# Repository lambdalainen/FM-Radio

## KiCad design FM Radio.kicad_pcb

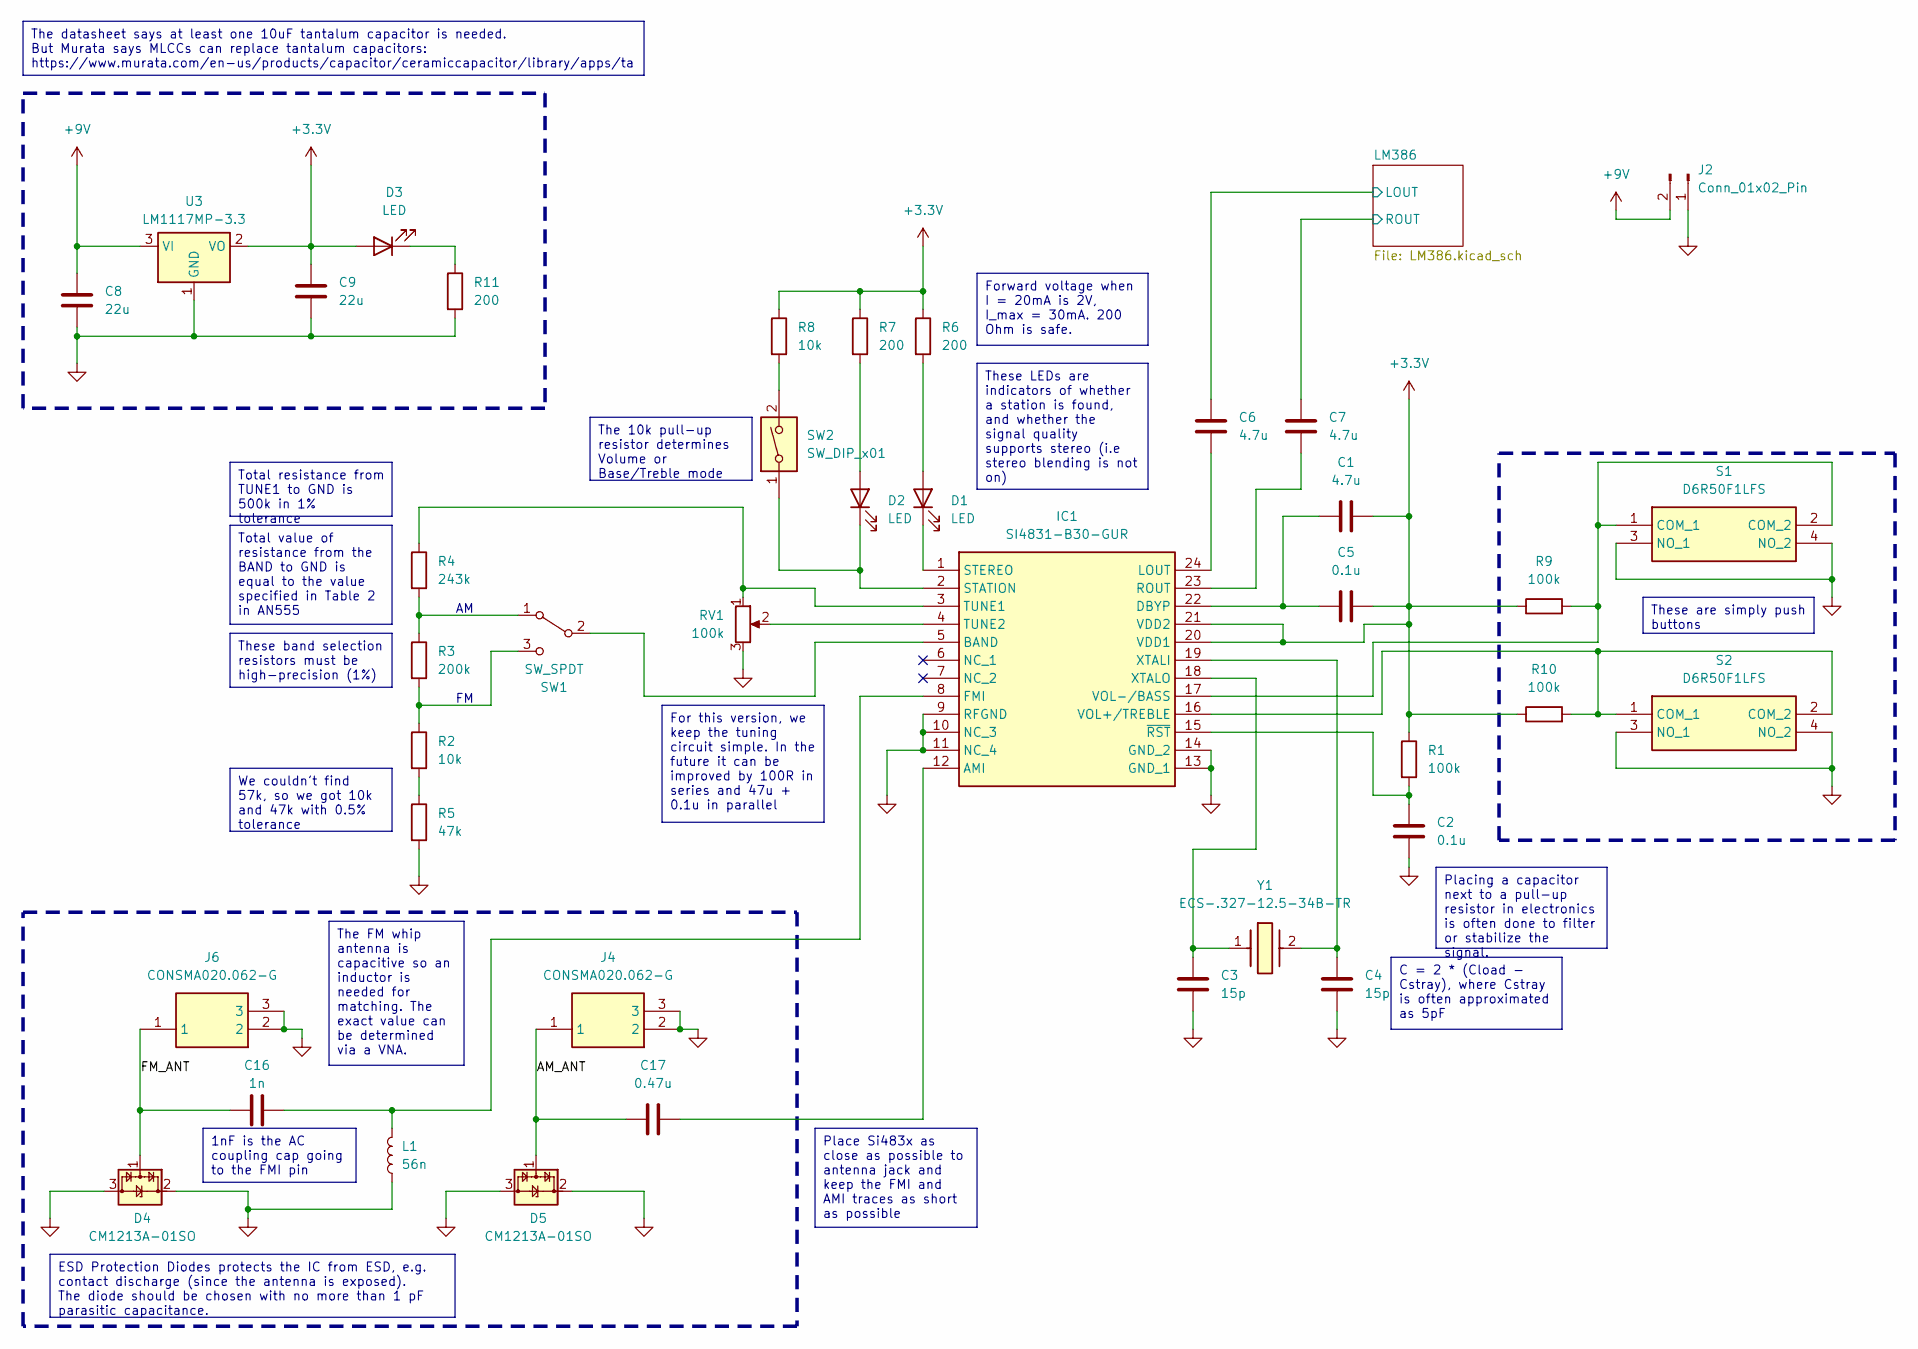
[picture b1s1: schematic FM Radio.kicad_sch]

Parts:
C1, C6, C7: 4.7u; C_0603_1608Metric
C2, C5: 0.1u; C_0603_1608Metric
C3, C4: 15p; C_0603_1608Metric
C8: 22u; C_0805_2012Metric
C9: 22u; CAPC2012X145N
C16: 1n; C_0603_1608Metric
C17: 0.47u; C_0603_1608Metric
D1, D2, D3: LED; LED_0603_1608Metric
D4, D5: CM1213A-01SO; SOT-23-3
IC1: SI4831-B30-GUR; SOP64P600X175-24N; Manufacturer_Part_Number SI4831-B30-GUR; Mouser Part Number 634-SI4831-B30-GUR
J2: Conn_01x02_Pin; PinHeader_1x02_P2.54mm_Vertical
J4, J6: CONSMA020.062-G; CONSMA020062G; Manufacturer_Part_Number CONSMA020.062-G; Mouser Part Number 712-CONSMA020.062-G
L1: 56n; L_0603_1608Metric
R1, R9, R10: 100k; R_0603_1608Metric
R2: 10k; R_0603_1608Metric
R3: 200k; R_0603_1608Metric
R4: 243k; R_0603_1608Metric
R5: 47k; R_0603_1608Metric
R6: 200; RESC1608X55N
R7, R11: 200; R_0603_1608Metric
R8: 10k; R_0603_1608Metric_Pad0.98x0.95mm_HandSolder
RV1: 100k; 91A1AB28B13L
S1, S2: D6R50F1LFS; D6R40F1LFS; Manufacturer_Part_Number D6R50F1LFS; Mouser Part Number 611-D6R50F1LFS
SW1: SW_SPDT; SW_SPDT_PCM12
SW2: SW_DIP_x01; DS01254L01BE
U3: LM1117MP-3.3; SOT-223-3_TabPin2
Y1: ECS-.327-12.5-34B-TR; ECX-31B; Manufacturer_Part_Number ECS-.327-12.5-34B-TR; Mouser Part Number 520-327-12.5-34B

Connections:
+3.3V: C1.2, C5.2, C9.2, D3.2 (A), IC1.20 (VDD1), IC1.21 (VDD2), R1.1, R6.1, R7.1, R8.1, R9.1, R10.1, U3.2 (VO)
/AM_ANT: C17.2, D5.1 (CH1), J4.1
/FM_ANT: C16.2, D4.1 (CH1), J6.1
/LM386/LOUT: C6.2; also elsewhere on the board
/LM386/ROUT: C7.2; also elsewhere on the board
GND: C2.2, C3.2, C4.2, C8.1, C9.1, D4.2 (VP), D4.3 (VN), D5.2 (VP), D5.3 (VN), IC1.9 (RFGND), IC1.10 (NC_3), IC1.11 (NC_4), IC1.13 (GND_1), IC1.14 (GND_2), J2.1, J4.2, J4.3, J6.2, J6.3, L1.1, R5.2, R11.2, RV1.3, S1.3 (NO_1), S1.4 (NO_2), S2.3 (NO_1), S2.4 (NO_2), U3.1 (GND); also elsewhere on the board
unnamed: D1.2 (A), R6.2
unnamed: D1.1 (K), IC1.1 (STEREO)
unnamed: D2.2 (A), R7.2
unnamed: D2.1 (K), IC1.2 (STATION), SW2.1
unnamed: D3.1 (K), R11.1
unnamed: C17.1, IC1.12 (AMI)
unnamed: IC1.5 (BAND), SW1.2 (B)
unnamed: C1.1, C5.1, IC1.22 (DBYP)
unnamed: C16.1, IC1.8 (FMI), L1.2
unnamed: C6.1, IC1.24 (LOUT)
unnamed: C7.1, IC1.23 (ROUT)
unnamed: IC1.3 (TUNE1), R4.1, RV1.1
unnamed: IC1.4 (TUNE2), RV1.2
unnamed: IC1.16 (VOL+/TREBLE), R10.2, S2.1 (COM_1), S2.2 (COM_2)
unnamed: IC1.17 (VOL-/BASS), R9.2, S1.1 (COM_1), S1.2 (COM_2)
unnamed: C4.1, IC1.19 (XTALI), Y1.2
unnamed: C3.1, IC1.18 (XTALO), Y1.1
unnamed: C2.1, IC1.15 (~RST), R1.2
unnamed: R2.2, R5.1
unnamed: R8.2, SW2.2
unnamed: R3.1, R4.2, SW1.1 (A)
unnamed: R2.1, R3.2, SW1.3 (C)

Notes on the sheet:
Placing a capacitor next to a pull-up resistor in electronics is often done to filter or stabilize the signal.
We couldn't find 57k, so we got 10k and 47k with 0.5% tolerance
These are simply push buttons
The FM whip antenna is capacitive so an inductor is needed for matching. The exact value can be determined via a VNA.
These LEDs are indicators of whether a station is found, and whether the signal quality supports stereo (i.e stereo blending is not on)
The 10k pull-up resistor determines Volume or Base/Treble mode
Place Si483x as close as possible to antenna jack and keep the FMI and AMI traces as short as possible
Total value of resistance from the BAND to GND is equal to the value specified in Table 2 in AN555
The datasheet says at least one 10uF tantalum capacitor is needed. But Murata says MLCCs can replace tantalum capacitors: https://www.murata.com/en-us/products/capacitor/ceramiccapacitor/library/apps/ta
These band selection resistors must be high-precision (1%)
For this version, we keep the tuning circuit simple. In the future it can be improved by 100R in series and 47u + 0.1u in parallel
1nF is the AC coupling cap going to the FMI pin
Forward voltage when I = 20mA is 2V, I_max = 30mA. 200 Ohm is safe.
Total resistance from TUNE1 to GND is 500k in 1% tolerance
ESD Protection Diodes protects the IC from ESD, e.g. contact discharge (since the antenna is exposed). The diode should be chosen with no more than 1 pF parasitic capacitance.
C = 2 * (Cload - Cstray), where Cstray is often approximated as 5pF

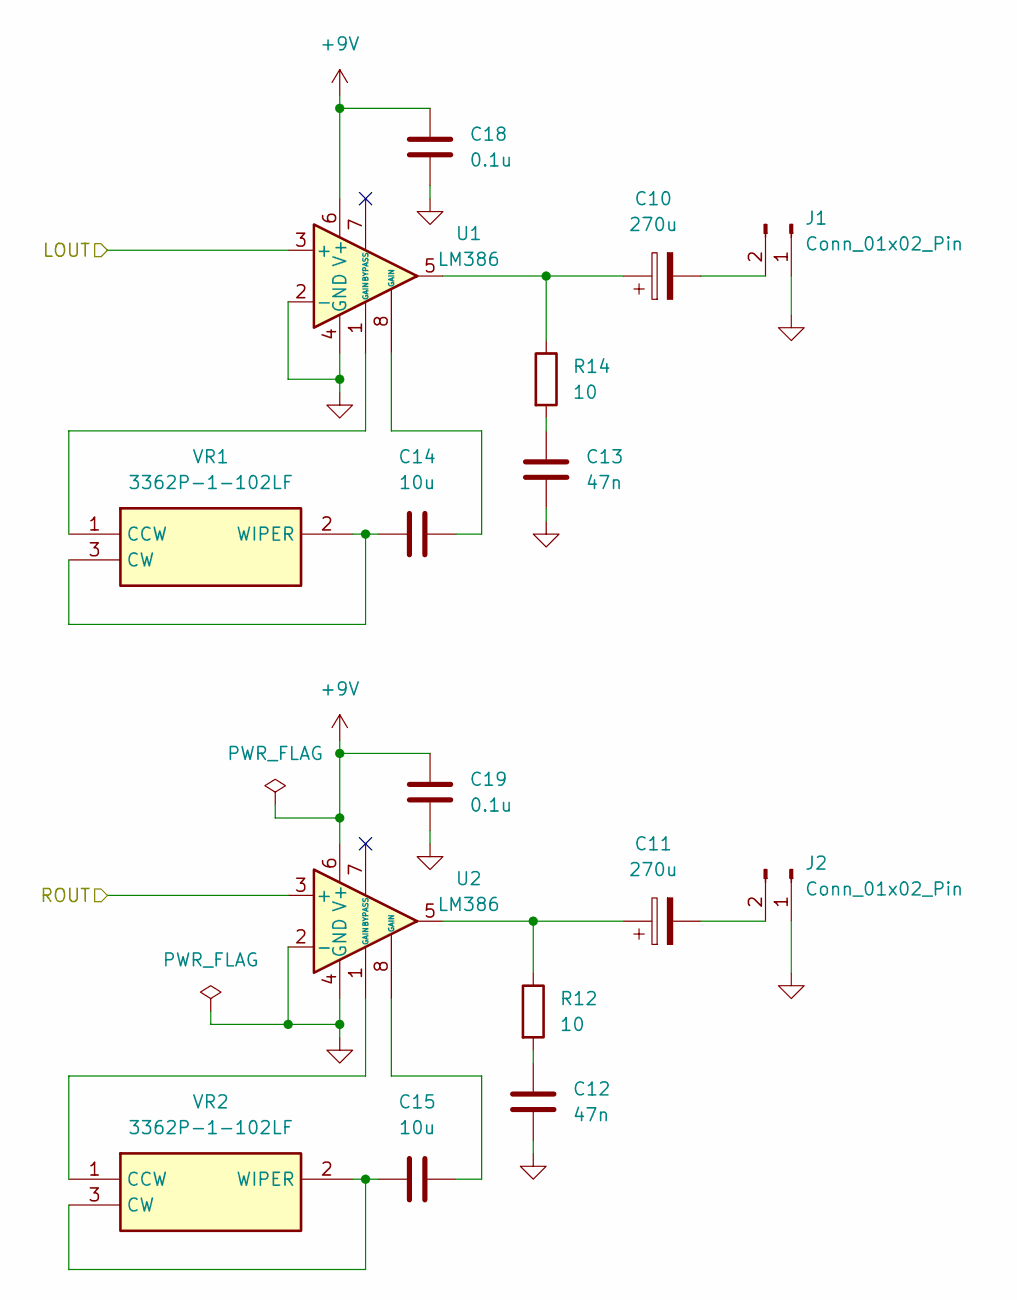
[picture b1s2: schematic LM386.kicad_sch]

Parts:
C10, C11: 270u; CP_Radial_D6.3mm_P2.50mm
C12, C13: 47n; C_0603_1608Metric
C14, C15: 10u; C_0603_1608Metric
C18, C19: 0.1u; C_0603_1608Metric
J1, J2: Conn_01x02_Pin; PinHeader_1x02_P2.54mm_Vertical
R12, R14: 10; R_0603_1608Metric
U1, U2: LM386; SOIC-8_3.9x4.9mm_P1.27mm
VR1, VR2: 3362P-1-102LF; 3362P_1; Manufacturer_Part_Number 3362P-1-102LF; Mouser Part Number 652-3362P-1-102LF

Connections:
/LM386/LOUT: U1.3 (+); also elsewhere on the board
/LM386/ROUT: U2.3 (+); also elsewhere on the board
GND: C12.2, C13.2, C18.1, C19.1, J1.1, J2.1, U1.2 (-), U1.4 (GND), U2.2 (-), U2.4 (GND); also elsewhere on the board
unnamed: C10.1, R14.1, U1.5
unnamed: C11.1, R12.1, U2.5
unnamed: C12.1, R12.2
unnamed: C13.1, R14.2
unnamed: C14.2, U1.8 (GAIN)
unnamed: C15.2, U2.8 (GAIN)
unnamed: C10.2, J1.2
unnamed: U1.1 (GAIN), VR1.1 (CCW)
unnamed: C14.1, VR1.2 (WIPER), VR1.3 (CW)
unnamed: U2.1 (GAIN), VR2.1 (CCW)
unnamed: C15.1, VR2.2 (WIPER), VR2.3 (CW)

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
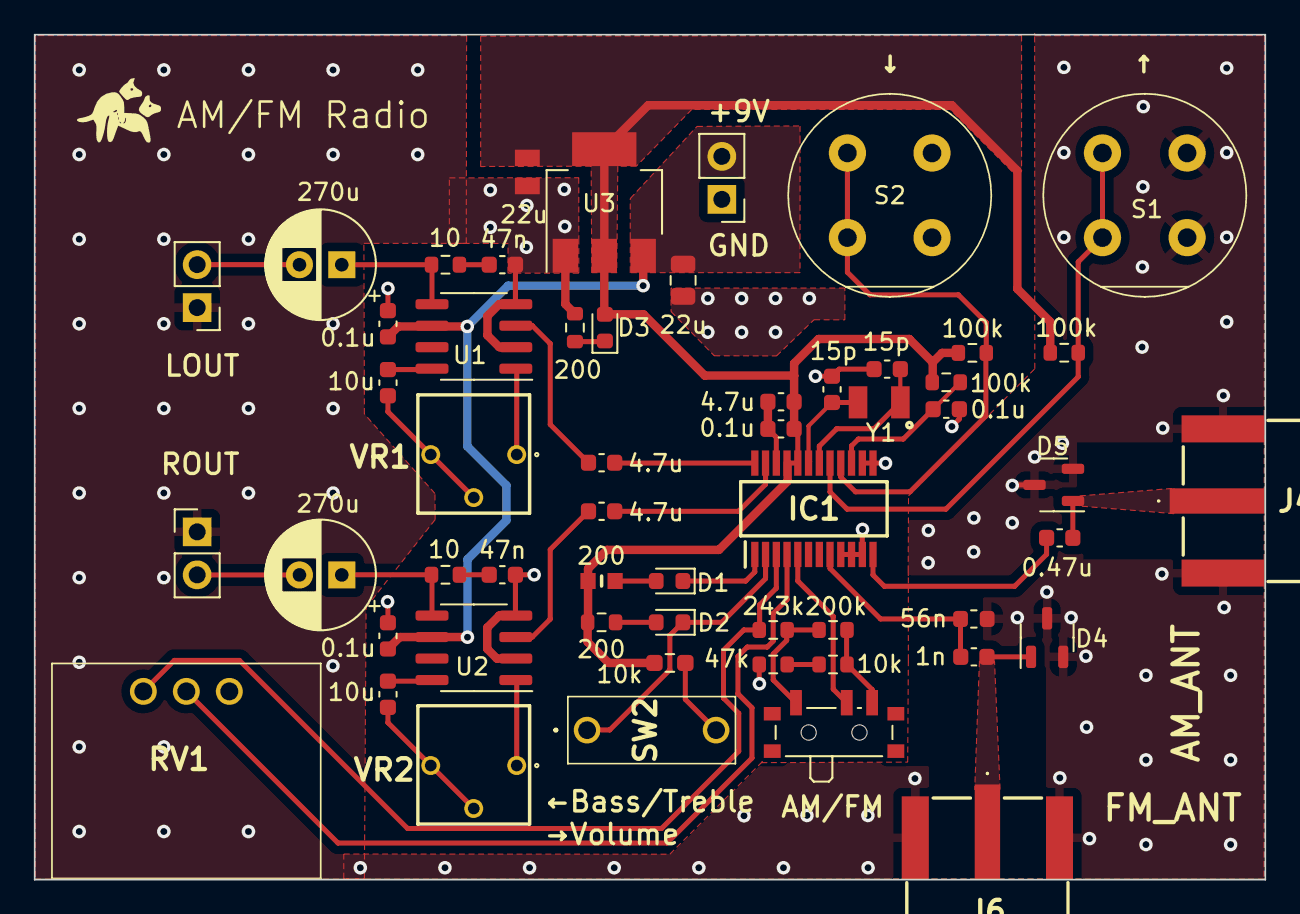
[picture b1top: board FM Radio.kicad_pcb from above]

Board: 2 copper layers, 72.7 x 49.9 mm, 55 parts (0 on the bottom side), 41 nets.

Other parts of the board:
J3: Conn_01x02_Pin; PinHeader_1x02_P2.54mm_Vertical

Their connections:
GND: J3.1; also elsewhere on the board

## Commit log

2024-01-25 Add 1k trimmer 3362P-1-102LF
2024-01-25 Add Micro USB Type B Connector 629105150521
2024-01-25 Add potentiometer
    We are using 91A1A-B28-A20L but could only find 91A1A-B28-A25L for footprint.
    They should be the same.
2024-01-25 Add SMA connector CONSMA020.062-G
2024-01-26 Add push button D6R50F1LFS (50 green, 40 red)
2024-01-26 Add 32.768 kHz crystal
2024-01-26 Add RESC1608X55N footprint (0603)
2024-01-26 Add CAPC2012X145N footprint (0805, 22 uF)
2024-01-26 Add DIP switch DS01-254-L-01BE
2024-01-26 Schematics done and footprint assigned
2024-01-27 Remove Micro USB Type B Connector 629105150521 as it is unused
2024-01-27 Add comments and fix errors
2024-01-27 Fix: VDD not connected
2024-01-27 Add JLCPCB rules
    https://gist.github.com/darkxst/f713268e5469645425eed40115fb8b49
2024-01-29 Generate KiCad design rules from JLCPCB rules
2024-01-29 Change footprint library path
2024-01-29 Fix grounding mistake with the trimmers
2024-01-29 Add bypass caps to LM386
2024-01-29 Very rough component placement
2024-02-04 Complete layout
2024-02-04 Plot Gerber
